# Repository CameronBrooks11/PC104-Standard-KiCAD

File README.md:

# PC104-Standard-KiCad #

This repository contains schematics and footprints of the PC/104 standard. 
These designs are compatible with KiCad PCB design software.
The footprints have also a suggested PCB boundary that facilitates the cable management of the CubeSat.

Derived from, although not affiliated with, [pc104.org](https://pc104.org/)

# TODO #
PC/104 Express, Plus, etc.

# KiCAD #

The KiCAD's schematic includes all the necessary pins assignments to speedup the payload design. The footprint already has the edge cuts done and it follows the PC104 specification.

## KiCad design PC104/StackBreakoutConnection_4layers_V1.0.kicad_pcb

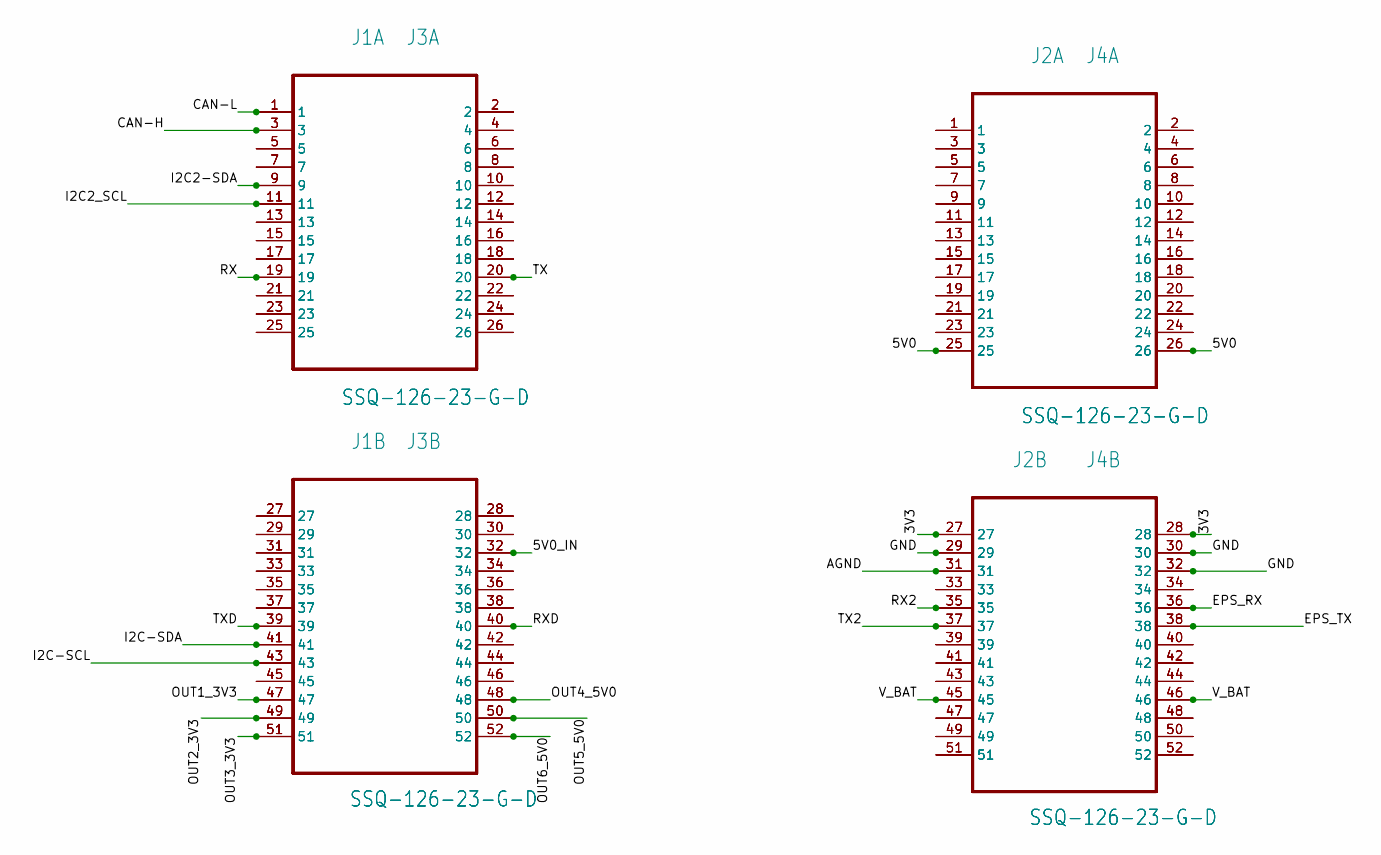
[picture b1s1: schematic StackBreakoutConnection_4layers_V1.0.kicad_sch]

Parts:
J1, J2, J3, J4: SSQ-126-23-G-D; SAMTEC_SSQ-126-23-G-D

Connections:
3V3: J2.27, J2.28, J4.27, J4.28
5V0: J2.25, J2.26, J4.25, J4.26
5V0_IN: J1.32, J3.32
AGND: J2.31, J4.31
CAN-H: J1.3, J3.3
CAN-L: J1.1, J3.1
EPS_RX: J2.36, J4.36
EPS_TX: J2.38, J4.38
GND: J2.29, J2.30, J2.32, J4.29, J4.30, J4.32
I2C2-SDA: J1.9, J3.9
I2C2_SCL: J1.11, J3.11
I2C-SCL: J1.43, J3.43
I2C-SDA: J1.41, J3.41
unnamed: J1.5, J3.5
unnamed: J1.7, J3.7
unnamed: J1.13, J3.13
unnamed: J1.15, J3.15
unnamed: J1.17, J3.17
unnamed: J1.21, J3.21
unnamed: J1.23, J3.23
unnamed: J1.25, J3.25
unnamed: J1.2, J3.2
unnamed: J1.4, J3.4
unnamed: J1.6, J3.6
unnamed: J1.8, J3.8
unnamed: J1.10, J3.10
unnamed: J1.12, J3.12
unnamed: J1.14, J3.14
unnamed: J1.16, J3.16
unnamed: J1.18, J3.18
unnamed: J1.22, J3.22
unnamed: J1.24, J3.24
unnamed: J1.26, J3.26
unnamed: J1.27, J3.27
unnamed: J1.29, J3.29
unnamed: J1.31, J3.31
unnamed: J1.33, J3.33
unnamed: J1.35, J3.35
unnamed: J1.37, J3.37
unnamed: J1.45, J3.45
unnamed: J1.28, J3.28
unnamed: J1.30, J3.30
unnamed: J1.34, J3.34
unnamed: J1.36, J3.36
unnamed: J1.38, J3.38
unnamed: J1.42, J3.42
unnamed: J1.44, J3.44
unnamed: J1.46, J3.46
unnamed: J2.1, J4.1
unnamed: J2.3, J4.3
unnamed: J2.5, J4.5
unnamed: J2.7, J4.7
unnamed: J2.9, J4.9
unnamed: J2.11, J4.11
unnamed: J2.13, J4.13
unnamed: J2.15, J4.15
unnamed: J2.17, J4.17
unnamed: J2.19, J4.19
unnamed: J2.21, J4.21
unnamed: J2.23, J4.23
unnamed: J2.2, J4.2
unnamed: J2.4, J4.4
unnamed: J2.6, J4.6
unnamed: J2.8, J4.8
unnamed: J2.10, J4.10
unnamed: J2.12, J4.12
unnamed: J2.14, J4.14
unnamed: J2.16, J4.16
unnamed: J2.18, J4.18
unnamed: J2.20, J4.20
unnamed: J2.22, J4.22
unnamed: J2.24, J4.24
unnamed: J2.33, J4.33
unnamed: J2.39, J4.39
unnamed: J2.41, J4.41
unnamed: J2.43, J4.43
unnamed: J2.47, J4.47
unnamed: J2.49, J4.49
unnamed: J2.51, J4.51
unnamed: J2.34, J4.34
unnamed: J2.40, J4.40
unnamed: J2.42, J4.42
unnamed: J2.44, J4.44
unnamed: J2.48, J4.48
unnamed: J2.50, J4.50
unnamed: J2.52, J4.52
OUT1_3V3: J1.47, J3.47
OUT2_3V3: J1.49, J3.49
OUT3_3V3: J1.51, J3.51
OUT4_5V0: J1.48, J3.48
OUT5_5V0: J1.50, J3.50
OUT6_5V0: J1.52, J3.52
RX: J1.19, J3.19
RX2: J2.35, J4.35
RXD: J1.40, J3.40
TX: J1.20, J3.20
TX2: J2.37, J4.37
TXD: J1.39, J3.39
V_BAT: J2.45, J2.46, J4.45, J4.46

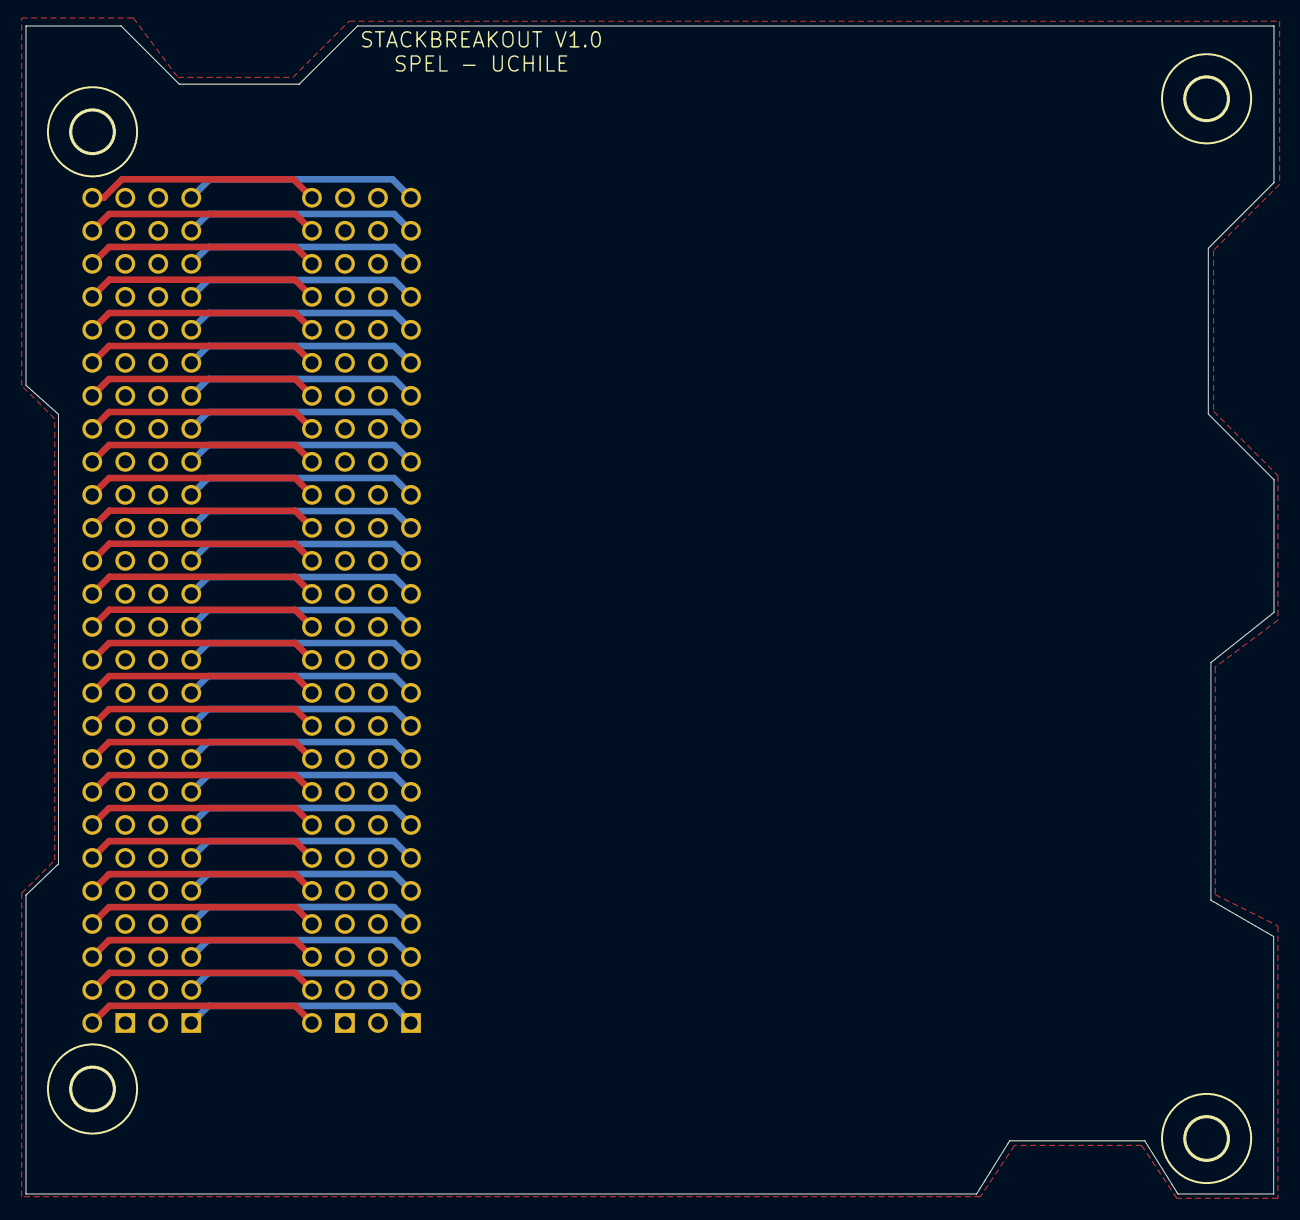
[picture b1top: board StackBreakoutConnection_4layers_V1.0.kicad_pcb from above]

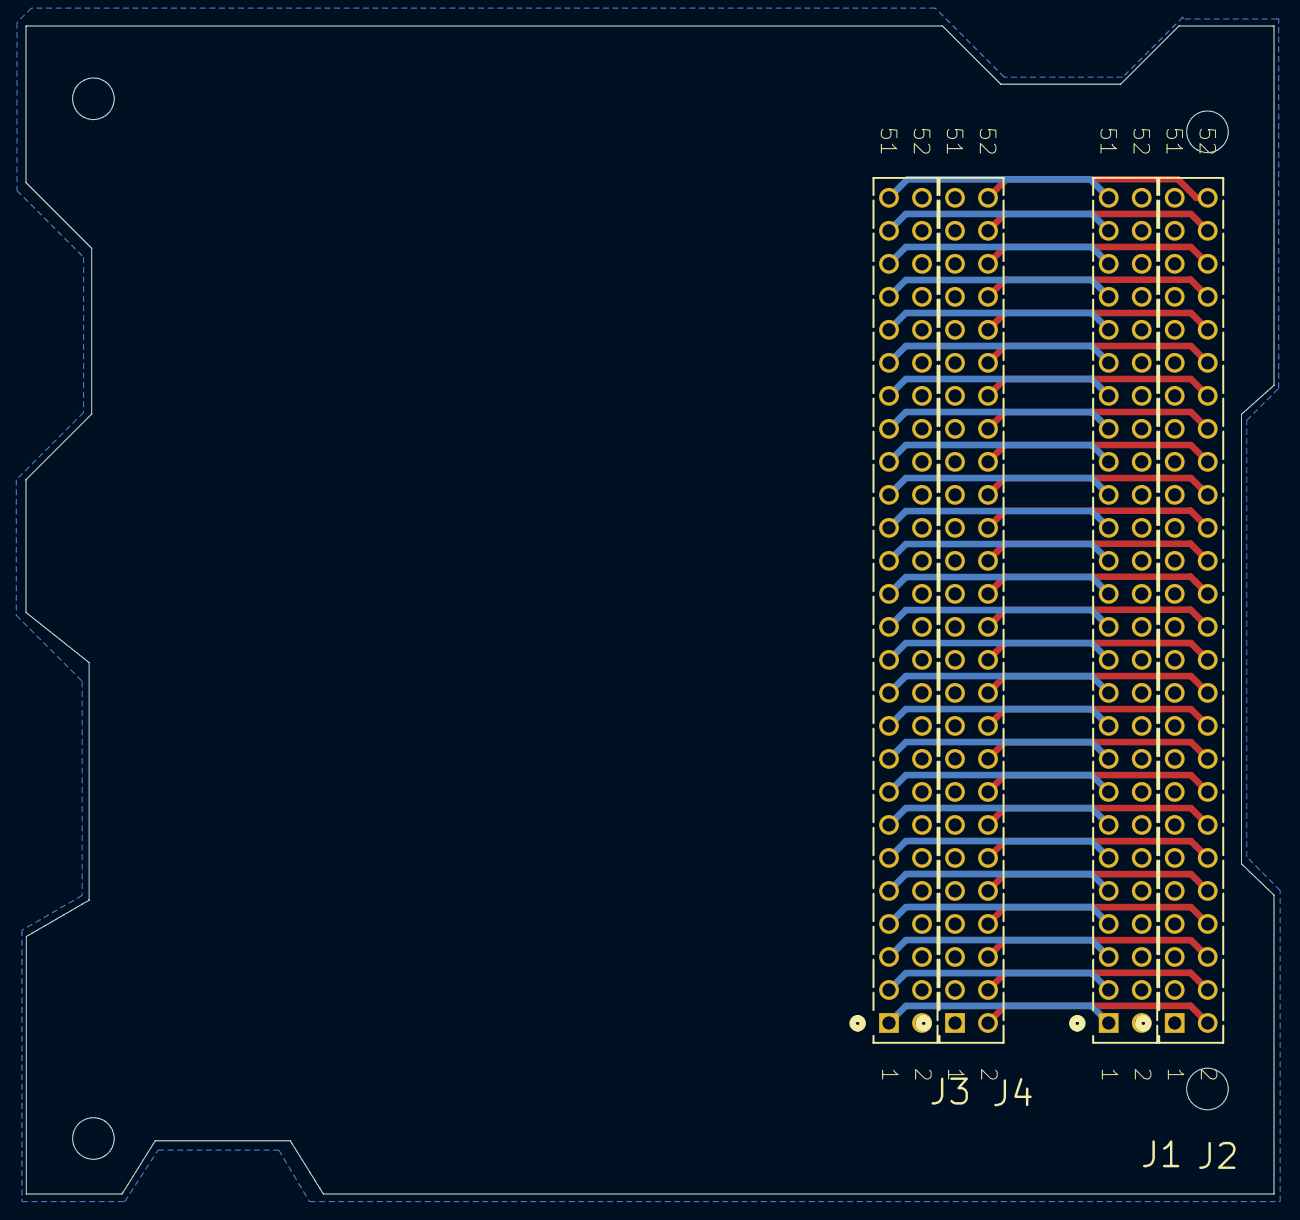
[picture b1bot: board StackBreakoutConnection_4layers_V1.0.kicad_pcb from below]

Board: 4 copper layers, 96.0 x 89.9 mm, 8 parts (4 on the bottom side), 99 nets.

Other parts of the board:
U$1, U$2, U$3, U$4: 3,2

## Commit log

2024-02-20 local push
